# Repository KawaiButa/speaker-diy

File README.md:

# DIY Active Stage Monitor Loudspeaker
### High-Efficiency, Low-Cost Active Wedge Monitor (Visaton BG 20 + TPA3255 PBTL)

A complete, open-hardware engineering design for a **DIY Active Stage Monitor Loudspeaker** optimized for live vocal and acoustic guitar performance at indoor venues (1–2 m listening distance). 

The design combines an ultra-efficient 8-inch full-range transducer with an analog front-end, active excursion protection, a commercial high-efficiency Class-D power amplifier, and a modular home-buildable prototyping architecture.

---

## Key System Specifications

| Parameter | Specification | Engineering Details & Rationale |
| :--- | :--- | :--- |
| **Acoustic Transducer** | Visaton BG 20 ($8\ \Omega$) | 8-inch full-range driver with whizzer cone, $92\text{ dB/W/m}$ sensitivity, $f_s = 38\text{ Hz}$. |
| **Linear Excursion Limit** | $\pm 2.0\text{ mm}$ ($X_{\text{max}}$) | Voice coil height $8\text{ mm}$, pole plate $4\text{ mm}$; continuous drive policy strictly capped at **10.0 W RMS** to prevent bottoming out. |
| **Continuous SPL Target** | $\ge 102\text{ dB}$ SPL @ 1 m ($96\text{ dB}$ @ 2 m) | Achieved cleanly at 10 W RMS without driver power compression or thermal stress. |
| **Power Amplifier** | Wuzhi ZK-3002 (TPA3255) | Preassembled Class-D module configured in **Parallel Bridge-Tied Load (PBTL)** mono. |
| **External Power Supply** | $36\text{ V} / 5\text{ A}$ ($180\text{ W}$) | Off-the-shelf regulated switch-mode DC adapter; low voltage entry into cabinet for safety. |
| **Reverse Polarity Protection**| IRF4905 P-MOSFET + 12V Zener | Forward drop $\le 25\text{ mV}$ ($0.5\text{ W}$ dissipation at 5A); blocks reverse DC up to $-55\text{ V}$ with zero leakage. |
| **Analog Power Rail** | $+15.0\text{ V}$ DC Linear Regulated | LM317HVT linear regulator ($V_{\text{in}} \le 60\text{ V}$) with diode protection and ripple rejection. |
| **Virtual Ground Rail** | $+7.50\text{ V}$ Active Buffer | Precision $10\text{ k}\Omega$ divider actively buffered by NE5532P op-amp follower. |
| **Microphone Preamplifier** | Gain $+20.0\text{ dB} \sim +50.5\text{ dB}$ | Balanced difference receiver ($U_{1\text{A}}$) + non-inverting gain stage ($U_{1\text{B}}$), $\ge 50\text{ dB}$ discrete CMRR. |
| **Line Differential Receiver**| Gain $-9.54\text{ dB}$ ($A_d = 0.333$) | Balanced difference receiver ($U_{2\text{B}}$) accepting $+4\text{ dBu}$ nominal with clean $+22\text{ dBu}$ headroom. |
| **Mode Switching** | DPDT Mechanical Selector | **Mode A:** Standalone Vocal (Mic Preamp active).<br>**Mode B:** Mixer Monitor (Line In active). |
| **Common Driver Protection** | 60 Hz 2nd-order Sallen-Key HPF | Butterworth $Q = 0.707$, $-3.0\text{ dB}$ @ $60\text{ Hz}$, $\ge 15.3\text{ dB}$ attenuation at 25 Hz. **Protects both Mic and Line paths.** |
| **Passive Contour Network** | Switchable RLC Filter | $1.0\text{ mH}$ air choke, $4.7\ \mu\text{F}$ MKP cap, $8.2\ \Omega / 10\text{ W}$ resistor. $-4.5\text{ dB}$ dip @ 1.5–2.5 kHz to tame whizzer cone. |
| **Enclosure** | 25 L Net Stage Wedge | 15 mm MDF, $45^\circ$ monitor angle, bass-reflex port tuned to $F_b = 50.0\text{ Hz} \pm 2\text{ Hz}$ (PVC tube $60\text{ mm}$ ID $\times 91.2\text{ mm}$). |
| **Total Weight & Budget** | $< 15\text{ kg}$, $< 5,000,000\text{ VND}$ | Estimated finished weight: $\approx 11.5\text{ kg}$; estimated total BOM: $\approx 3,725,000\text{ VND}$. |

---

## System Architecture

```
                                  +---------------------------------------------+
                                  | 36V 5A External DC Power Adapter (Switching)|
                                  +---------------------------------------------+
                                                         | (DC Barrel Jack J3)
                                                         v
                                  +---------------------------------------------+
                                  | Panel Fuse F1 (5x20mm 4A-T Cartridge)       |
                                  +---------------------------------------------+
                                                         | [18 AWG Red Silicone]
                                                         v
                                  +---------------------------------------------+
                                  | BOARD B: Power Conditioning (5x7 cm)        |
                                  | - Q1: IRF4905 P-FET Reverse Polarity Protect|
                                  | - C17: 470uF/50V Bulk Reservoir Capacitor   |
                                  | - U4: LM317HVT Linear Regulator (+15V Out)  |
                                  | - U3: NE5532P Active Virtual Ground (+7.5V) |
                                  +---------------------------------------------+
                                        |                             |
                   [18 AWG Heavy DC]    |                             | [22 AWG +15V, +7.5V, GND]
                   +36V & Power GND     |                             | Clean Analog Rails
                                        v                             v
+---------------------------------------------+         +---------------------------------------------+
| Wuzhi ZK-3002 (TPA3255 PBTL Mono Amplifier) |         | BOARD A: Analog Audio Front-End (7x9 cm)    |
| - High-current Class-D switching module     |         | - U1: NE5532P (Mic Preamp, Gain +20..+50dB) |
| - External preassembled heatsink & caps     |         | - U2: NE5532P (Line Rec -9.5dB, 60Hz HPF)   |
| - PBTL Mode: Pin 1 IN+ (Sig), Pin 2 IN- (GND)|         | - Inputs: XLR J1 (Mic), Combo J2 (Line)     |
+---------------------------------------------+         | - Controls: RV1 Gain, RV2/RV3 Vol, SW1 Mode |
        |                      ^                        +---------------------------------------------+
        | Floating PBTL        | Shielded Audio Coax                          |
        | Speaker Audio        | J5 Pin 1 Sig / Pin 2 GND                     |
        | [18 AWG Orange/Blue] +----------------------------------------------+
        v
+---------------------------------------------+
| BOARD C: Passive Speaker Filter (5x7 cm)    |
| - L1: 1.0 mH Air-Core Choke (1.0mm wire)    |
| - R23: 8.2 Ohm 10W Non-Inductive Resistor   |
| - C24: 4.7 uF 250V MKP Film Capacitor       |
| - SW2: Heavy-Duty SPST Contour Bypass Switch|
| * STRICT RULE: ZERO GROUND CONNECTIONS!     |
+---------------------------------------------+
        |
        | [18 AWG Direct Speaker Leads]
        v
+---------------------------------------------+
| Transducer: Visaton BG 20 (8 Ohm, 8-inch)   |
| Continuous Power Limit: 10.0 W RMS          |
| Enclosure: 25 L Net MDF Wedge (Fb = 50 Hz)  |
+---------------------------------------------+
```

---

## Modular Hardware Implementation

This project is specifically designed to be **built at home without custom PCB manufacturing, CNC milling, or chemical etching**.

All circuits are partitioned across standard **FR-4 double-sided universal prototyping boards ($2.54\text{ mm}$ pitch, isolated tinned pads)**:

### 1. Board B — Power Conditioning & +7.5V Bias Reference ($5 \times 7\text{ cm}$)
- **Dimensions:** 18 Columns (A–R) $\times$ 24 Rows (1–24).
- **Functions:** IRF4905 P-FET reverse-polarity protection, LM317HVT $+15.0\text{ V}$ linear regulator, and NE5532P active buffer producing low-impedance $+7.50\text{ V}$ virtual ground.
- **Assembly Guide:** [`gate-e-board-b-assembly.svg`](projects/live-pa-system/gate-e-board-b-assembly.svg)

### 2. Board A — Audio Analog Front-End ($7 \times 9\text{ cm}$)
- **Dimensions:** 26 Columns (A–Z) $\times$ 31 Rows (1–31).
- **Functions:**
  - **Zone 1 (Left):** Balanced Microphone Differential Preamp (U1, XLR J1, RV1 Gain pot, RV2 Volume pot).
  - **Zone 2 (Right):** Balanced Line Receiver (U2B, Combo J2, RV3 Line pot), Mode Selector Switch (SW1), and Master 60 Hz 2nd-order Sallen-Key HPF (U2A).
- **Assembly Guide:** [`gate-e-board-a-assembly.svg`](projects/live-pa-system/gate-e-board-a-assembly.svg)

### 3. Board C — Passive Speaker Filter ($5 \times 7\text{ cm}$)
- **Dimensions:** 18 Columns (A–R) $\times$ 24 Rows (1–24).
- **Functions:** Heavy-duty RLC contour notch network ($1.0\text{ mH}$, $4.7\ \mu\text{F}$, $8.2\ \Omega / 10\text{ W}$) with bypass switch (SW2).
- **CRITICAL SAFETY RULE:** **ZERO ground connections.** Both PBTL speaker outputs float at $+18.0\text{ V}$ DC half-supply.
- **Assembly Guide:** [`gate-e-board-c-assembly.svg`](projects/live-pa-system/gate-e-board-c-assembly.svg)

---

## Phased Procurement & Verification Plan

Procurement and hardware testing follow a strict **7-stage gated workflow**. No downstream components are purchased until the preceding subsystem is tested and confirmed passed:

```
+========================================================================================================================+
| BATCH | SUBSYSTEM DESCRIPTION              | ESTIMATED COST   | CUMULATIVE   | REMAINING BUDGET | GATE STATUS          |
+========================================================================================================================+
| B-0   | Tools & Construction Consumables   |      180,000 VND |  180,000 VND |    4,820,000 VND | READY (ACTIVE)       |
| B-1   | Board B: Power & +7.5V Bias Buffer |      195,000 VND |  375,000 VND |    4,625,000 VND | READY (ACTIVE)       |
| B-2   | Board A (Zone 1): Mic Preamp       |      140,000 VND |  515,000 VND |    4,485,000 VND | BLOCKED (Wait Gate 1)|
| B-3   | Board A (Zone 2): Line Rec & HPF   |      150,000 VND |  665,000 VND |    4,335,000 VND | BLOCKED (Wait Gate 2)|
| B-4   | TPA3255 Amp, 36V PSU & Dummy Load  |      800,000 VND | 1,465,000 VND|    3,535,000 VND | BLOCKED (Wait Gate 3)|
| B-5   | Visaton BG 20 & 25L MDF Enclosure  |    1,860,000 VND | 3,325,000 VND|    1,675,000 VND | BLOCKED (Wait Gate 4)|
| B-6   | Board C: RLC Contour & Finishing   |      400,000 VND | 3,725,000 VND|    1,275,000 VND | BLOCKED (Wait Gate 5)|
+========================================================================================================================+
| TOTAL ESTIMATED PROJECT INVESTMENT: 3,725,000 VND | HARD BUDGET LIMIT: 5,000,000 VND | CONTINGENCY RESERVE: +1,275,000 VND     |
+========================================================================================================================+
```

For detailed purchasing checklists and Vietnamese search keywords for Shopee/Lazada/Thegioiic, see [`gate-e-phased-shopping-plan.md`](projects/live-pa-system/gate-e-phased-shopping-plan.md).

---

## Project Directory Structure

```
speaker-diy/
├── README.md                                 # Project overview, specifications, and quickstart
├── .gitignore                                # KiCad, Python, and OS ignore patterns
├── projects/
│   └── live-pa-system/                       # Primary active monitor engineering project
│       ├── live-pa-system.kicad_sch          # Authoritative KiCad 10 schematic (42 nets, 73 components)
│       ├── live-pa-system.net                # Exported netlist
│       ├── live-pa-system.cir                # SPICE netlist for ngspice verification
│       ├── live-pa-system.kicad_pro          # KiCad project file
│       ├── gate-d-design-report.md           # Gate D engineering report & simulation audit
│       ├── gate-e-phased-shopping-plan.md    # Phased 7-batch procurement & testing plan
│       ├── gate-e-bench-testing-plan.md      # Detailed bench testing, thermal & acoustic test plan
│       ├── gate-e-protoboard-wiring.md       # Master hole-by-hole point-to-point wiring schedule
│       ├── gate-e-board-a-assembly.svg       # Scaled assembly diagram: Board A (Audio Front-End)
│       ├── gate-e-board-b-assembly.svg       # Scaled assembly diagram: Board B (Power & Bias Buffer)
│       ├── gate-e-board-c-assembly.svg       # Scaled assembly diagram: Board C (Passive RLC Filter)
│       ├── gate-e-system-wiring-diagram.svg  # Overall system interconnect wiring diagram
│       └── simulation/                       # ngspice dedicated testbenches and simulation logs
└── .agents/                                  # Specialized electronics and speaker design agent skills
```

---

## Critical Safety & Bring-Up Rules

> [!CAUTION]
> 1. **Current-Limited Power-Up:** Never connect newly assembled prototype boards directly to an unrestricted battery or power supply. Use a bench supply with current limit set to $100\text{ mA}$, or insert a **$100\ \Omega / 10\text{ W}$ power resistor** in series with the $+36\text{ V}$ adapter lead during initial bring-up to clamp short-circuit fault current to $\le 360\text{ mA}$.
> 2. **Floating PBTL Speaker Bridge Outputs:** The Wuzhi ZK-3002 / TPA3255 PBTL output operates as an active H-bridge. **Both output terminals float at $+18.0\text{ V}$ DC half-supply.** Never connect either speaker output to signal ground, chassis ground, or an oscilloscope ground clip!
> 3. **LM317HVT Heatsink Tab Isolation:** The TO-220 metal mounting tab of `U4` is internally connected to **Pin 2 (Output, $+15\text{ V}$)**, NOT ground! The heatsink must remain electrically floating with $\ge 3\text{ mm}$ clearance from adjacent components and chassis ground.
> 4. **18 AWG Direct Power Wiring:** 36V 5A DC power and speaker audio lines must never run over thin perfboard copper foil. Use direct, insulated **18 AWG stranded silicone wire**.

---

## License

This project is licensed under the [MIT License](LICENSE) — hardware schematics, wiring schedules, and documentation are provided openly for DIY audio enthusiasts and educational purposes.

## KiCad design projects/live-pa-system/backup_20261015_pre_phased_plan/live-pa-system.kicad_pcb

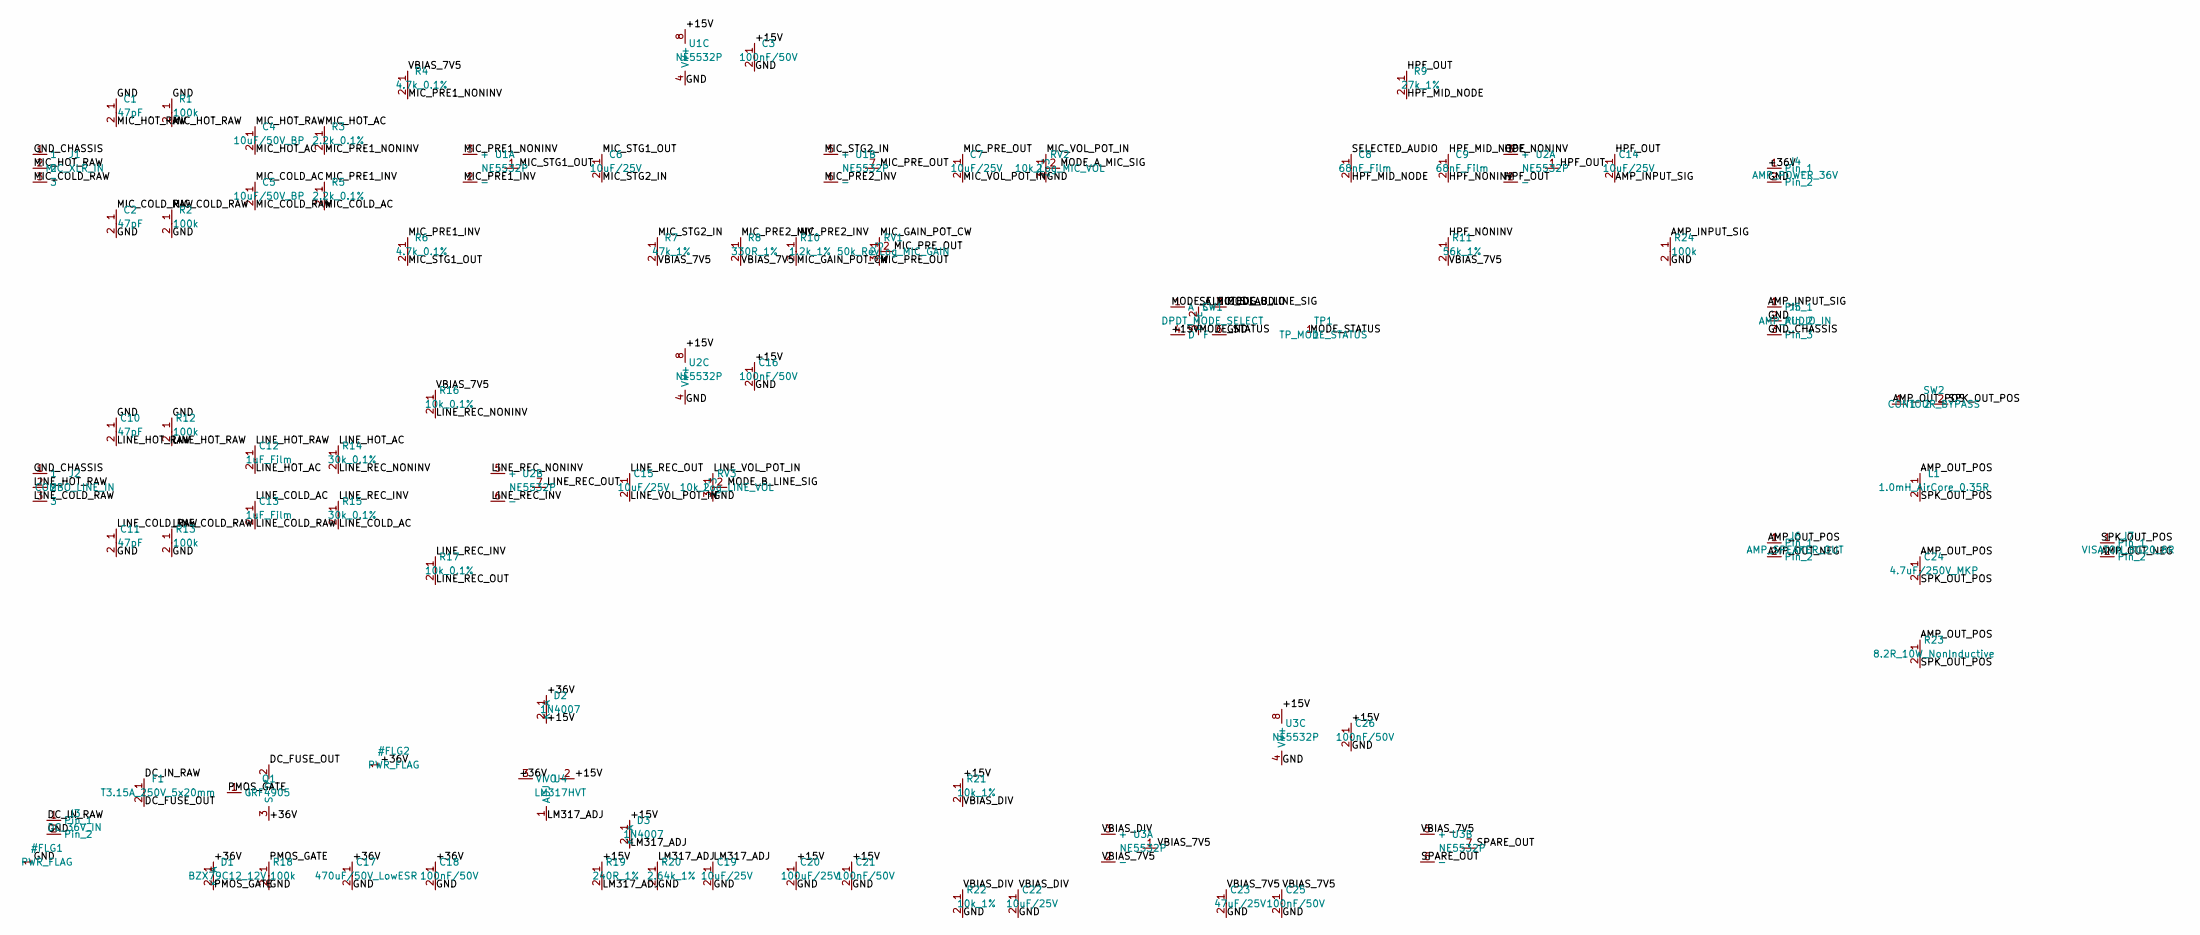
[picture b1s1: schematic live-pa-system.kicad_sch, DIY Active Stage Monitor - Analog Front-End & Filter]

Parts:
C1, C2, C10, C11: 47pF; C_Disc_D4.3mm_W1.9mm_P5.00mm
C3, C16, C18, C21, C25, C26: 100nF/50V; C_Rect_L7.2mm_W2.5mm_P5.00mm_FKS2_FKP2_MKS2_MKP2
C4, C5: 10uF/50V_BP; CP_Radial_D6.3mm_P2.50mm
C6, C7, C14, C15, C19, C22: 10uF/25V; CP_Radial_D5.0mm_P2.00mm
C8, C9: 68nF_Film; C_Rect_L7.2mm_W3.5mm_P5.00mm_FKS2_FKP2_MKS2_MKP2
C12, C13: 1uF_Film; C_Rect_L7.2mm_W3.5mm_P5.00mm_FKS2_FKP2_MKS2_MKP2
C17: 470uF/50V_LowESR; CP_Radial_D10.0mm_P5.00mm
C20: 100uF/25V; CP_Radial_D6.3mm_P2.50mm
C23: 47uF/25V; CP_Radial_D5.0mm_P2.00mm
C24: 4.7uF/250V_MKP; C_Rect_L18.0mm_W9.0mm_P15.00mm_FKS3_FKP3
D1: BZX79C12_12V; D_DO-35_SOD27_P7.62mm_Horizontal
D2, D3: 1N4007; D_DO-41_SOD81_P10.16mm_Horizontal
F1: T3.15A_250V_5x20mm; Fuseholder_Cylinder-5x20mm_Schurter_0031_8201_Horizontal_Op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
J1: MIC_XLR_IN; Jack_XLR_Neutrik_NC3FAH_Horizontal
J2: COMBO_LINE_IN; Jack_XLR-6.35mm_Neutrik_NCJ6FI-H_Horizontal
J3: DC_36V_IN; BarrelJack_Horizontal
J4: AMP_POWER_36V; TerminalBlock_Phoenix_MKDS-1,5-2-5.08_1x02_P5.08mm_Horizont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
J5: AMP_AUDIO_IN; PinHeader_1x03_P2.54mm_Vertical
J6: AMP_SPEAKER_OUT; TerminalBlock_Phoenix_MKDS-1,5-2-5.08_1x02_P5.08mm_Horizont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
J7: VISATON_BG20_8R; TerminalBlock_Phoenix_MKDS-1,5-2-5.08_1x02_P5.08mm_Horizont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
L1: 1.0mH_AirCore_0.35R; L_Radial_D27.9mm_P19.05mm_Vishay_IHB-3
Q1: IRF4905; TO-220-3_Vertical
R1, R2, R12, R13, R18, R24: 100k; R_Axial_DIN0207_L6.3mm_D2.5mm_P7.62mm_Horizontal
R3, R5: 2.2k_0.1%; R_Axial_DIN0207_L6.3mm_D2.5mm_P7.62mm_Horizontal
R4, R6: 4.7k_0.1%; R_Axial_DIN0207_L6.3mm_D2.5mm_P7.62mm_Horizontal
R7: 47k_1%; R_Axial_DIN0207_L6.3mm_D2.5mm_P7.62mm_Horizontal
R8: 330R_1%; R_Axial_DIN0207_L6.3mm_D2.5mm_P7.62mm_Horizontal
R9: 27k_1%; R_Axial_DIN0207_L6.3mm_D2.5mm_P7.62mm_Horizontal
R10: 1.2k_1%; R_Axial_DIN0207_L6.3mm_D2.5mm_P7.62mm_Horizontal
R11: 56k_1%; R_Axial_DIN0207_L6.3mm_D2.5mm_P7.62mm_Horizontal
R14, R15: 30k_0.1%; R_Axial_DIN0207_L6.3mm_D2.5mm_P7.62mm_Horizontal
R16, R17: 10k_0.1%; R_Axial_DIN0207_L6.3mm_D2.5mm_P7.62mm_Horizontal
R19: 240R_1%; R_Axial_DIN0207_L6.3mm_D2.5mm_P7.62mm_Horizontal
R20: 2.64k_1%; R_Axial_DIN0207_L6.3mm_D2.5mm_P7.62mm_Horizontal
R21, R22: 10k_1%; R_Axial_DIN0207_L6.3mm_D2.5mm_P7.62mm_Horizontal
R23: 8.2R_10W_NonInductive; R_Axial_Power_L25.0mm_W9.0mm_P30.48mm
RV1: 50k_RevLog_MIC_GAIN; Potentiometer_Bourns_3386P_Vertical
RV2: 10k_Log_MIC_VOL; Potentiometer_Bourns_3386P_Vertical
RV3: 10k_Log_LINE_VOL; Potentiometer_Bourns_3386P_Vertical
SW1: DPDT_MODE_SELECT; SW_CK_JS202011CQN_DPDT_Straight
SW2: CONTOUR_BYPASS; SW_DIP_SPSTx01_Slide_6.7x4.1mm_W7.62mm_P2.54mm_LowProfile
TP1: TP_MODE_STATUS; TestPoint_Pad_D1.5mm
U1, U2, U3: NE5532P; DIP-8_W7.62mm
U4: LM317HVT; TO-220-3_Vertical

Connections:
+15V: C3.1, C16.1, C20.1, C21.1, C26.1, D2.2 (A), D3.1 (K), R19.1, R21.1, SW1.4 (D), U1.8 (V+), U2.8 (V+), U3.8 (V+), U4.2 (VO)
+36V: C17.1, C18.1, D1.1 (K), D2.1 (K), J4.1, Q1.3 (S), U4.3 (VI)
AMP_INPUT_SIG: C14.2, J5.1, R24.1
AMP_OUT_NEG: J6.2, J7.2
AMP_OUT_POS: C24.1, J6.1, L1.1, R23.1, SW2.1
DC_FUSE_OUT: F1.2, Q1.2 (D)
DC_IN_RAW: F1.1, J3.1
GND: C1.1, C2.2, C3.2, C10.1, C11.2, C16.2, C17.2, C18.2, C19.2, C20.2, C21.2, C22.2, C23.2, C25.2, C26.2, J3.2, J4.2, J5.2, R1.1, R2.2, R12.1, R13.2, R18.2, R20.2, R22.2, R24.2, RV2.3, RV3.3, SW1.6 (F), U1.4 (V-), U2.4 (V-), U3.4 (V-)
GND_CHASSIS: J1.1, J2.1, J5.3
HPF_MID_NODE: C8.2, C9.1, R9.2
HPF_NONINV: C9.2, R11.1, U2.3 (+)
HPF_OUT: C14.1, R9.1, U2.1, U2.2 (-)
LINE_COLD_AC: C13.1, R15.2
LINE_COLD_RAW: C11.1, C13.2, J2.3, R13.1
LINE_HOT_AC: C12.2, R14.1
LINE_HOT_RAW: C10.2, C12.1, J2.2, R12.2
LINE_REC_INV: R15.1, R17.1, U2.6 (-)
LINE_REC_NONINV: R14.2, R16.2, U2.5 (+)
LINE_REC_OUT: C15.1, R17.2, U2.7
LINE_VOL_POT_IN: C15.2, RV3.1
LM317_ADJ: C19.1, D3.2 (A), R19.2, R20.1, U4.1 (ADJ)
MIC_COLD_AC: C5.1, R5.2
MIC_COLD_RAW: C2.1, C5.2, J1.3, R2.1
MIC_GAIN_POT_CW: R10.2, RV1.1
MIC_HOT_AC: C4.2, R3.1
MIC_HOT_RAW: C1.2, C4.1, J1.2, R1.2
MIC_PRE1_INV: R5.1, R6.1, U1.2 (-)
MIC_PRE1_NONINV: R3.2, R4.2, U1.3 (+)
MIC_PRE2_INV: R8.1, R10.1, U1.6 (-)
MIC_PRE_OUT: C7.1, RV1.2, RV1.3, U1.7
MIC_STG1_OUT: C6.1, R6.2, U1.1
MIC_STG2_IN: C6.2, R7.1, U1.5 (+)
MIC_VOL_POT_IN: C7.2, RV2.1
MODE_A_MIC_SIG: RV2.2, SW1.1 (A)
MODE_B_LINE_SIG: RV3.2, SW1.3 (C)
MODE_STATUS: SW1.5 (E), TP1.1
PMOS_GATE: D1.2 (A), Q1.1 (G), R18.1
SELECTED_AUDIO: C8.1, SW1.2 (B)
SPARE_OUT: U3.6 (-), U3.7
SPK_OUT_POS: C24.2, J7.1, L1.2, R23.2, SW2.2
VBIAS_7V5: C23.1, C25.1, R4.1, R7.2, R8.2, R11.2, R16.1, U3.1, U3.2 (-), U3.5 (+)
VBIAS_DIV: C22.1, R21.2, R22.1, U3.3 (+)

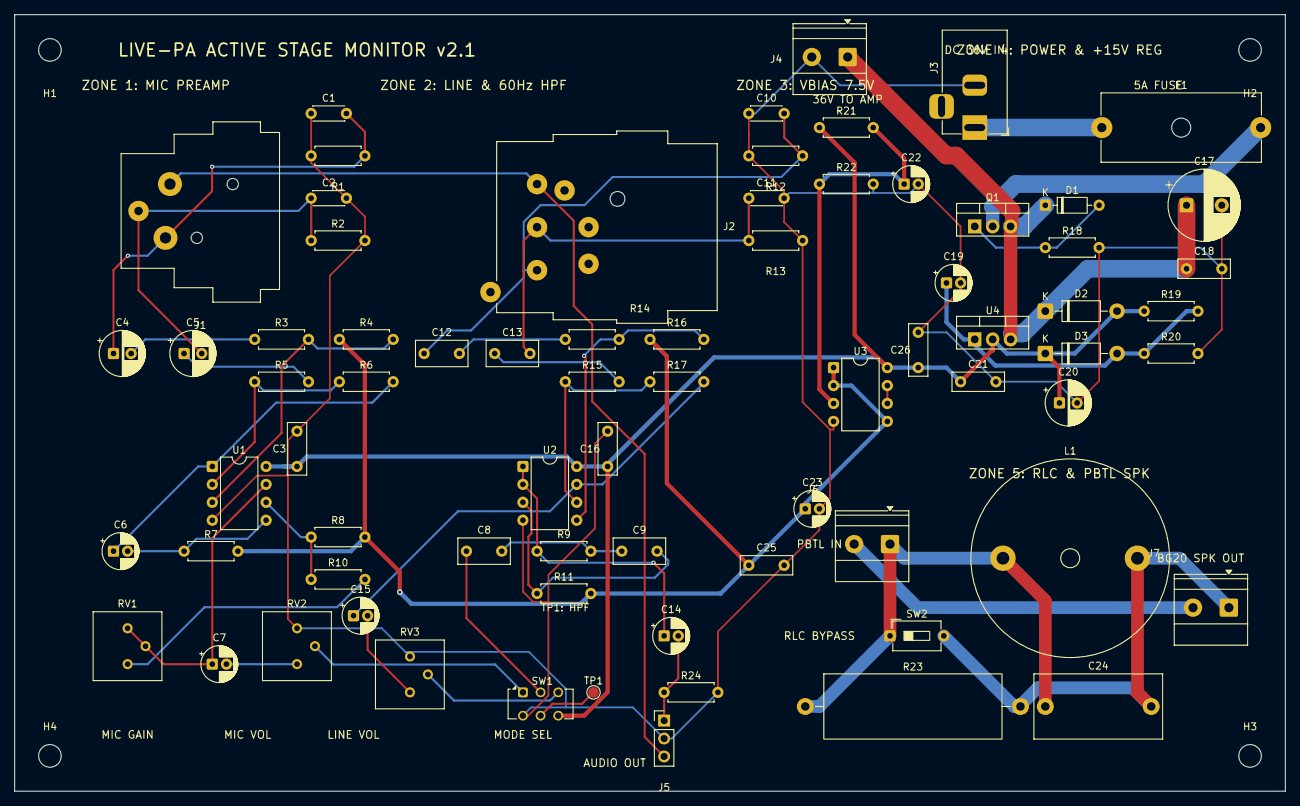
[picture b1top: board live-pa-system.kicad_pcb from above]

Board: 2 copper layers, 180.0 x 110.0 mm, 77 parts (0 on the bottom side), 42 nets.

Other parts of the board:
H1, H2, H3, H4: MountingHole_3.2mm_M3

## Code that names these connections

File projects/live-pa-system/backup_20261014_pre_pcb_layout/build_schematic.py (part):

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    j1_x, j1_y = snap(40.0), snap(50.0) # 40.64, 50.80
    add_sym("Connector_Audio:XLR3_Female", "J1", "MIC_XLR_IN", j1_x, j1_y, "Connector_Audio:Jack_XLR_Neutrik_NC3FAH_Horizontal")
    connect_pin(j1_x - 5.08, j1_y - 2.54, "GND_CHASSIS")
    connect_pin(j1_x - 5.08, j1_y,        "MIC_HOT_RAW")
    connect_pin(j1_x - 5.08, j1_y + 2.54, "MIC_COLD_RAW")

    # RF Filter Caps C1, C2
    c1_x, c1_y = snap(52.0), snap(40.0) # 50.80, 40.64
    add_sym("Device:C", "C1", "47pF", c1_x, c1_y, "Capacitor_THT:C_Disc_D4.3mm_W1.9mm_P5.00mm")
    connect_pin(c1_x, c1_y - 2.54, "GND")
    connect_pin(c1_x, c1_y + 2.54, "MIC_HOT_RAW")

    c2_x, c2_y = snap(52.0), snap(60.0) # 50.80, 60.96
    add_sym("Device:C", "C2", "47pF", c2_x, c2_y, "Capacitor_THT:C_Disc_D4.3mm_W1.9mm_P5.00mm")
    connect_pin(c2_x, c2_y - 2.54, "MIC_COLD_RAW")
    connect_pin(c2_x, c2_y + 2.54, "GND")

    # Bleeder Resistors R1, R2
    r1_x, r1_y = snap(62.0), snap(40.0) # 60.96, 40.64
    add_sym("Device:R", "R1", "100k", r1_x, r1_y, "Resistor_THT:R_Axial_DIN0207_L6.3mm_D2.5mm_P7.62mm_Horizontal")
    connect_pin(r1_x, r1_y - 2.54, "GND")
    connect_pin(r1_x, r1_y + 2.54, "MIC_HOT_RAW")

    r2_x, r2_y = snap(62.0), snap(60.0) # 60.96, 60.96
    add_sym("Device:R", "R2", "100k", r2_x, r2_y, "Resistor_THT:R_Axial_DIN0207_L6.3mm_D2.5mm_P7.62mm_Horizontal")
    connect_pin(r2_x, r2_y - 2.54, "MIC_COLD_RAW")
    connect_pin(r2_x, r2_y + 2.54, "GND")

    # AC Input Coupling Caps C4, C5 (Bipolar 10uF/50V)
    c4_x, c4_y = snap(76.0), snap(45.0) # 76.20, 45.72
    add_sym("Device:C_Polarized", "C4", "10uF/50V_BP", c4_x, c4_y, "Capacitor_THT:CP_Radial_D6.3mm_P2.50mm")
    connect_pin(c4_x, c4_y - 2.54, "MIC_HOT_RAW")
    connect_pin(c4_x, c4_y + 2.54, "MIC_HOT_AC")

    c5_x, c5_y = snap(76.0), snap(55.0) # 76.20, 55.88
    add_sym("Device:C_Polarized", "C5", "10uF/50V_BP", c5_x, c5_y, "Capacitor_THT:CP_Radial_D6.3mm_P2.50mm")
    connect_pin(c5_x, c5_y - 2.54, "MIC_COLD_AC")
    connect_pin(c5_x, c5_y + 2.54, "MIC_COLD_RAW")

    # Stage 1A Differential Resistors: Rin=2.2k 0.1%, Rfb/Rbias=4.7k 0.1% (High CMRR!)
    r3_x, r3_y = snap(90.0), snap(45.0) # 88.90, 45.72
    add_sym("Device:R", "R3", "2.2k_0.1%", r3_x, r3_y, "Resistor_THT:R_Axial_DIN0207_L6.3mm_D2.5mm_P7.62mm_Horizontal")
    connect_pin(r3_x, r3_y - 2.54, "MIC_HOT_AC")
    connect_pin(r3_x, r3_y + 2.54, "MIC_PRE1_NONINV")

    r5_x, r5_y = snap(90.0), snap(55.0) # 88.90, 55.88
    add_sym("Device:R", "R5", "2.2k_0.1%", r5_x, r5_y, "Resistor_THT:R_Axial_DIN0207_L6.3mm_D2.5mm_P7.62mm_Horizontal")
    connect_pin(r5_x, r5_y - 2.54, "MIC_PRE1_INV")
    connect_pin(r5_x, r5_y + 2.54, "MIC_COLD_AC")

    r4_x, r4_y = snap(104.0), snap(35.0) # 104.14, 35.56
    add_sym("Device:R", "R4", "4.7k_0.1%", r4_x, r4_y, "Resistor_THT:R_Axial_DIN0207_L6.3mm_D2.5mm_P7.62mm_Horizontal")
    connect_pin(r4_x, r4_y - 2.54, "VBIAS_7V5")
    connect_pin(r4_x, r4_y + 2.54, "MIC_PRE1_NONINV")

    r6_x, r6_y = snap(104.0), snap(65.0) # 104.14, 66.04
    add_sym("Device:R", "R6", "4.7k_0.1%", r6_x, r6_y, "Resistor_THT:R_Axial_DIN0207_L6.3mm_D2.5mm_P7.62mm_Horizontal")
    connect_pin(r6_x, r6_y - 2.54, "MIC_PRE1_INV")
    connect_pin(r6_x, r6_y + 2.54, "MIC_STG1_OUT")

    # U1A: Stage 1A Differential Op-Amp (Unit 1)
    u1a_x, u1a_y = snap(120.0), snap(50.0) # 119.38, 50.80
    add_sym("Amplifier_Operational:NE5532", "U1", "NE5532P", u1a_x, u1a_y, "Package_DIP:DIP-8_W7.62mm", unit=1)
    connect_pin(u1a_x - 5.08, u1a_y - 2.54, "MIC_PRE1_NONINV") # Pin 3 (+)
    connect_pin(u1a_x - 5.08, u1a_y + 2.54, "MIC_PRE1_INV")    # Pin 2 (-)
    connect_pin(u1a_x + 5.08, u1a_y,        "MIC_STG1_OUT")    # Pin 1 (Out)

    # Interstage Coupling: C6 (10uF), R7 (47k to Vbias)
    c6_x, c6_y = snap(140.0), snap(50.0) # 139.70, 50.80
    add_sym("Device:C_Polarized", "C6", "10uF/25V", c6_x, c6_y, "Capacitor_THT:CP_Radial_D5.0mm_P2.00mm")
    connect_pin(c6_x, c6_y - 2.54, "MIC_STG1_OUT")
    connect_pin(c6_x, c6_y + 2.54, "MIC_STG2_IN")

    r7_x, r7_y = snap(150.0), snap(65.0) # 149.86, 66.04
    add_sym("Device:R", "R7", "47k_1%", r7_x, r7_y, "Resistor_THT:R_Axial_DIN0207_L6.3mm_D2.5mm_P7.62mm_Horizontal")
    connect_pin(r7_x, r7_y - 2.54, "MIC_STG2_IN")
    connect_pin(r7_x, r7_y + 2.54, "VBIAS_7V5")

    # Stage 1B Variable Gain Feedback: Rgain=330R, Rfb2=1.2k, RV1=50k RevLog
    r8_x, r8_y = snap(165.0), snap(65.0) # 165.10, 66.04
    add_sym("Device:R", "R8", "330R_1%", r8_x, r8_y, "Resistor_THT:R_Axial_DIN0207_L6.3mm_D2.5mm_P7.62mm_Horizontal")
    connect_pin(r8_x, r8_y - 2.54, "MIC_PRE2_INV")
    connect_pin(r8_x, r8_y + 2.54, "VBIAS_7V5")

    r10_x, r10_y = snap(175.0), snap(65.0) # 175.26, 66.04
    add_sym("Device:R", "R10", "1.2k_1%", r10_x, r10_y, "Resistor_THT:R_Axial_DIN0207_L6.3mm_D2.5mm_P7.62mm_Horizontal")
    connect_pin(r10_x, r10_y - 2.54, "MIC_PRE2_INV")
    connect_pin(r10_x, r10_y + 2.54, "MIC_GAIN_POT_CW")

    rv1_x, rv1_y = snap(190.0), snap(65.0) # 190.50, 66.04
    add_sym("Device:R_Potentiometer", "RV1", "50k_RevLog_MIC_GAIN", rv1_x, rv1_y, "Potentiometer_THT:Potentiometer_Bourns_3386P_Vertical")
    connect_pin(rv1_x, rv1_y - 2.54, "MIC_GAIN_POT_CW") # Pin 1
    connect_pin(rv1_x + 2.54, rv1_y, "MIC_PRE_OUT")     # Pin 2 (wiper)
    connect_pin(rv1_x, rv1_y + 2.54, "MIC_PRE_OUT")     # Pin 3

    # U1B: Stage 1B Post-Amp (Unit 2)
    u1b_x, u1b_y = snap(185.0), snap(50.0) # 185.42, 50.80
    add_sym("Amplifier_Operational:NE5532", "U1", "NE5532P", u1b_x, u1b_y, "Package_DIP:DIP-8_W7.62mm", unit=2)
    connect_pin(u1b_x - 5.08, u1b_y - 2.54, "MIC_STG2_IN")  # Pin 5 (+)
    connect_pin(u1b_x - 5.08, u1b_y + 2.54, "MIC_PRE2_INV")  # Pin 6 (-)
    connect_pin(u1b_x + 5.08, u1b_y,        "MIC_PRE_OUT")   # Pin 7 (Out)

    # U1 Power (Unit 3) + Decoupling C3
    u1c_x, u1c_y = snap(155.0), snap(30.0) # 154.94, 30.48
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    # Mic Channel AC Coupling C7 & Dedicated Mic Volume Pot RV2
    c7_x, c7_y = snap(205.0), snap(50.0) # 205.74, 50.80
    add_sym("Device:C_Polarized", "C7", "10uF/25V", c7_x, c7_y, "Capacitor_THT:CP_Radial_D5.0mm_P2.00mm")
    connect_pin(c7_x, c7_y - 2.54, "MIC_PRE_OUT")
    connect_pin(c7_x, c7_y + 2.54, "MIC_VOL_POT_IN")

    rv2_x, rv2_y = snap(220.0), snap(50.0) # 220.98, 50.80
    add_sym("Device:R_Potentiometer", "RV2", "10k_Log_MIC_VOL", rv2_x, rv2_y, "Potentiometer_THT:Potentiometer_Bourns_3386P_Vertical")
    connect_pin(rv2_x, rv2_y - 2.54, "MIC_VOL_POT_IN") # Pin 1
    connect_pin(rv2_x + 2.54, rv2_y, "MODE_A_MIC_SIG")  # Pin 2 (wiper to Mode Switch)
    connect_pin(rv2_x, rv2_y + 2.54, "GND")             # Pin 3

    # =========================================================================
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    j2_x, j2_y = snap(40.0), snap(110.0) # 40.64, 109.22
    add_sym("Connector_Audio:XLR3_Female", "J2", "COMBO_LINE_IN", j2_x, j2_y, "Connector_Audio:Jack_XLR-6.35mm_Neutrik_NCJ6FI-H_Horizontal")
    connect_pin(j2_x - 5.08, j2_y - 2.54, "GND_CHASSIS")
    connect_pin(j2_x - 5.08, j2_y,        "LINE_HOT_RAW")
    connect_pin(j2_x - 5.08, j2_y + 2.54, "LINE_COLD_RAW")

    # RF Filter Caps C10, C11
    c10_x, c10_y = snap(52.0), snap(100.0) # 50.80, 99.06
    add_sym("Device:C", "C10", "47pF", c10_x, c10_y, "Capacitor_THT:C_Disc_D4.3mm_W1.9mm_P5.00mm")
    connect_pin(c10_x, c10_y - 2.54, "GND")
    connect_pin(c10_x, c10_y + 2.54, "LINE_HOT_RAW")

    c11_x, c11_y = snap(52.0), snap(120.0) # 50.80, 119.38
    add_sym("Device:C", "C11", "47pF", c11_x, c11_y, "Capacitor_THT:C_Disc_D4.3mm_W1.9mm_P5.00mm")
    connect_pin(c11_x, c11_y - 2.54, "LINE_COLD_RAW")
    connect_pin(c11_x, c11_y + 2.54, "GND")

    # Bleeder Resistors R12, R13
    r12_x, r12_y = snap(62.0), snap(100.0) # 60.96, 99.06
    add_sym("Device:R", "R12", "100k", r12_x, r12_y, "Resistor_THT:R_Axial_DIN0207_L6.3mm_D2.5mm_P7.62mm_Horizontal")
    connect_pin(r12_x, r12_y - 2.54, "GND")
    connect_pin(r12_x, r12_y + 2.54, "LINE_HOT_RAW")

    r13_x, r13_y = snap(62.0), snap(120.0) # 60.96, 119.38
    add_sym("Device:R", "R13", "100k", r13_x, r13_y, "Resistor_THT:R_Axial_DIN0207_L6.3mm_D2.5mm_P7.62mm_Horizontal")
    connect_pin(r13_x, r13_y - 2.54, "LINE_COLD_RAW")
    connect_pin(r13_x, r13_y + 2.54, "GND")

    # AC Input Coupling Caps C12, C13 (Film 1uF/63V)
    c12_x, c12_y = snap(76.0), snap(105.0) # 76.20, 104.14
    add_sym("Device:C", "C12", "1uF_Film", c12_x, c12_y, "Capacitor_THT:C_Rect_L7.2mm_W3.5mm_P5.00mm_FKS2_FKP2_MKS2_MKP2")
    connect_pin(c12_x, c12_y - 2.54, "LINE_HOT_RAW")
    connect_pin(c12_x, c12_y + 2.54, "LINE_HOT_AC")

    c13_x, c13_y = snap(76.0), snap(115.0) # 76.20, 114.30
    add_sym("Device:C", "C13", "1uF_Film", c13_x, c13_y, "Capacitor_THT:C_Rect_L7.2mm_W3.5mm_P5.00mm_FKS2_FKP2_MKS2_MKP2")
    connect_pin(c13_x, c13_y - 2.54, "LINE_COLD_AC")
    connect_pin(c13_x, c13_y + 2.54, "LINE_COLD_RAW")

    # Balanced Line Differential Attenuator: Rin=30k 0.1%, Rfb=10k 0.1% (Ad = 1/3 = -9.54 dB, High CMRR)
    r14_x, r14_y = snap(92.0), snap(105.0) # 91.44, 104.14
    add_sym("Device:R", "R14", "30k_0.1%", r14_x, r14_y, "Resistor_THT:R_Axial_DIN0207_L6.3mm_D2.5mm_P7.62mm_Horizontal")
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

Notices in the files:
README.md:
License: MIT
